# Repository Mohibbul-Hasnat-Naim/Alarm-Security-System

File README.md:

# Alarm-Security-System
This is demo of password based security system with Arduino.

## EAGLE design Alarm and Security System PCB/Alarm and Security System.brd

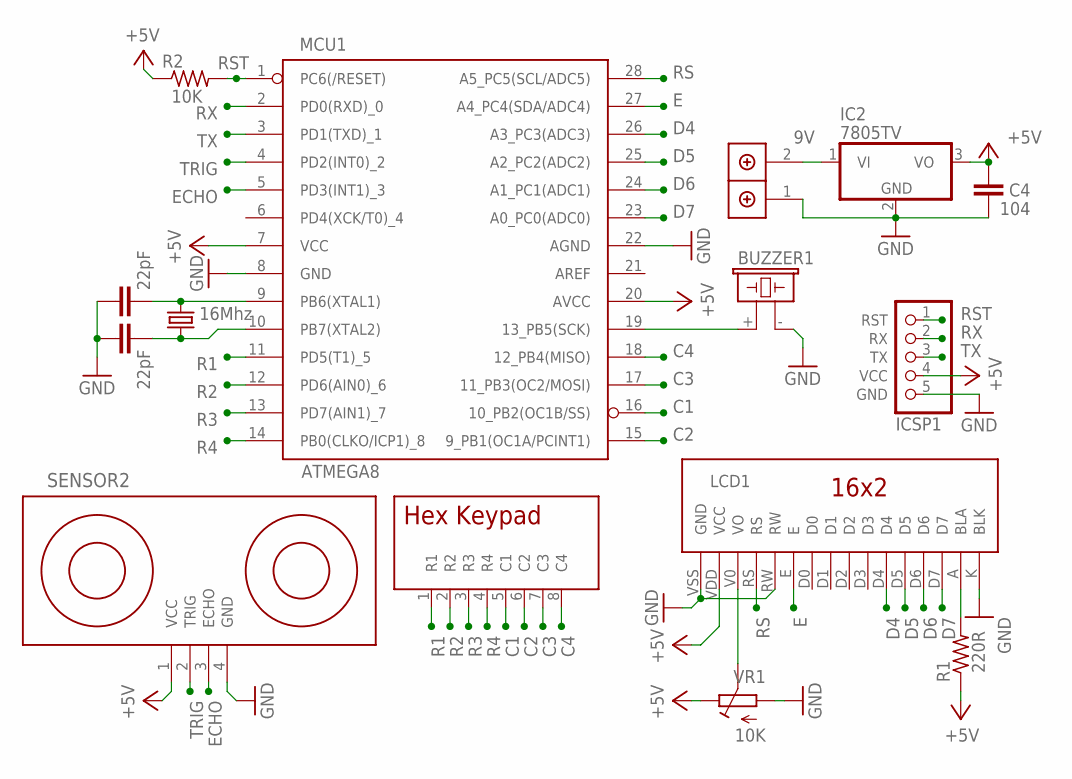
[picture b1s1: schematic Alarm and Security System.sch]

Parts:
BUZZER1: F/CM12P
C1, C2: 22pF; 22PF
C4: 104
IC2: 7805TV; TO220V
ICSP1: ICSP_ATMEGA328; ICSP_ATMEGA
KEYPAD1: HEX_KEYPAD
LCD1: 16X2_LCD
MCU1: ATMEGA8; ATMEGA328_P
Q1: 16Mhz; CRYSTAL
R1: 220R; THR_R_204/7
R2: 10K; THR_R_204/7
SENSOR2: ULTRASONIC-HC-SR04SONAR; 1X04
TB2: 2P
VR1: 10K; BLUE_VR

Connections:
9V: IC2.1 (VI), TB2.2 (CONN2)
+5V: C4.1, IC2.3 (VO), ICSP1.4 (VCC), LCD1.VDD (VCC), MCU1.7 (VCC), MCU1.20 (AVCC), R1.1, R2.1, SENSOR2.1 (VCC), VR1.1
C1: KEYPAD1.5 (C1), MCU1.16 (10_PB2(OC1B/SS))
C2: KEYPAD1.6 (C2), MCU1.15 (9_PB1(OC1A/PCINT1))
C3: KEYPAD1.7 (C3), MCU1.17 (11_PB3(OC2/MOSI))
C4: KEYPAD1.8 (C4), MCU1.18 (12_PB4(MISO))
D4: LCD1.D4, MCU1.26 (A3_PC3(ADC3))
D5: LCD1.D5, MCU1.25 (A2_PC2(ADC2))
D6: LCD1.D6, MCU1.24 (A1_PC1(ADC1))
D7: LCD1.D7, MCU1.23 (A0_PC0(ADC0))
E: LCD1.E, MCU1.27 (A4_PC4(SDA/ADC4))
ECHO: MCU1.5 (PD3(INT1)_3), SENSOR2.3 (ECHO)
GND: BUZZER1.- (2), C1.1, C2.2, C4.2, IC2.2 (GND), ICSP1.5 (GND), LCD1.K (BLK), LCD1.RW, LCD1.VSS (GND), MCU1.8 (GND), MCU1.22 (AGND), SENSOR2.4 (GND), TB2.1 (CONN1), VR1.3
unnamed: C1.2, MCU1.9 (PB6(XTAL1)), Q1.2
unnamed: C2.1, MCU1.10 (PB7(XTAL2)), Q1.1
unnamed: LCD1.A (BLA), R1.2
unnamed: LCD1.V0 (VO), VR1.2
unnamed: BUZZER1.+ (1), MCU1.19 (13_PB5(SCK))
R1: KEYPAD1.1 (R1), MCU1.11 (PD5(T1)_5)
R2: KEYPAD1.2 (R2), MCU1.12 (PD6(AIN0)_6)
R3: KEYPAD1.3 (R3), MCU1.13 (PD7(AIN1)_7)
R4: KEYPAD1.4 (R4), MCU1.14 (PB0(CLKO/ICP1)_8)
RS: LCD1.RS, MCU1.28 (A5_PC5(SCL/ADC5))
RST: ICSP1.1 (RST), MCU1.1 (PC6(/RESET)), R2.2
RX: ICSP1.2 (RX), MCU1.2 (PD0(RXD)_0)
TRIG: MCU1.4 (PD2(INT0)_2), SENSOR2.2 (TRIG)
TX: ICSP1.3 (TX), MCU1.3 (PD1(TXD)_1)

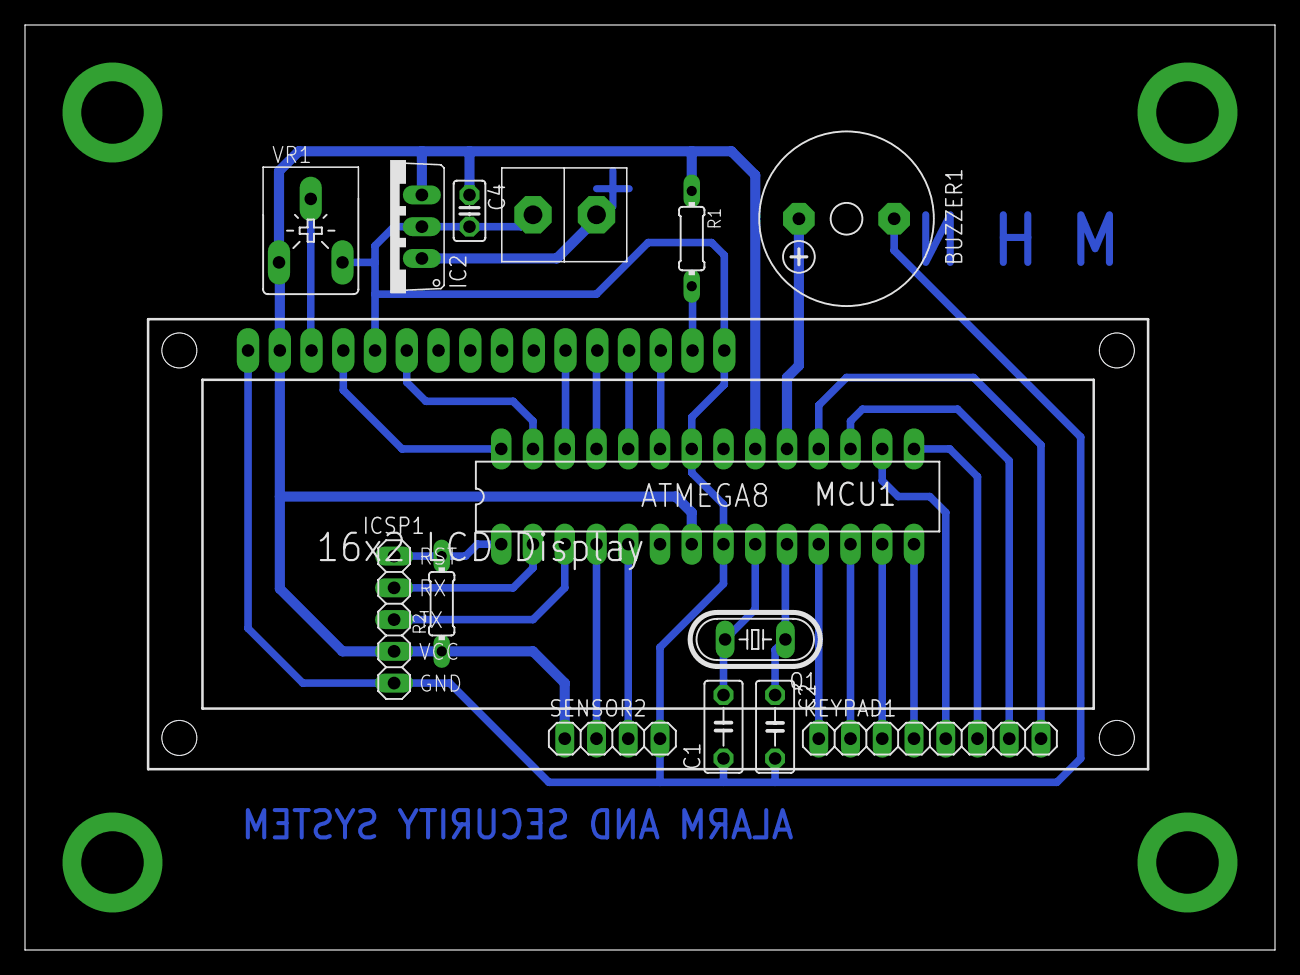
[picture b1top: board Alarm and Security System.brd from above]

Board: 2 copper layers, 100.0 x 74.0 mm, 15 parts (0 on the bottom side), 27 nets.
